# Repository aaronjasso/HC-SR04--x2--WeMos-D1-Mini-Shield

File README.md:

# HC-SR04--x2--WeMos-D1-Mini-Shield
Shield to attach up to two HC-SR04 ultrasonic distance sensors to a Wemos D1 Mini ESP8266 module.

[Sensor datasheet](https://cdn.sparkfun.com/datasheets/Sensors/Proximity/HCSR04.pdf)

[Second datasheet source](https://www.electroschematics.com/8902/hc-sr04-datasheet/)

Works with one or two sensors. The first is mounted to the shield, the second is intended to be mounted elsewhere and connected with a four-conductor cable. It could also be mounted directly to the board facing the opposite direction as the first sensor.

Utilizes a BS138DW SOT-363 chip (which is just two BSS138 N-channel enhanced mode MOSFETs in one package) for level switching the ESP8266's 3.3V trigger pulse up to 5V for the sensors (ref: https://learn.sparkfun.com/tutorials/retired---using-the-logic-level-converter). The down-convert is a simple voltage divider.

All resistors are 0805 size. Resistors on top of board (with the IC) are 10K, resistors on bottom are 20K.

SENSE1 is mounted to the board  
Trigger pin:  D3  
Echo pin:  D4

SENSE2 (optional) can be located off-board  
Trigger pin:  D7  
Echo pin:  D8

The board and SENSE1 have been tested. Example Arduino sketches are in work. Boards available from OSH Park here: https://oshpark.com/shared_projects/YeCIIDGi

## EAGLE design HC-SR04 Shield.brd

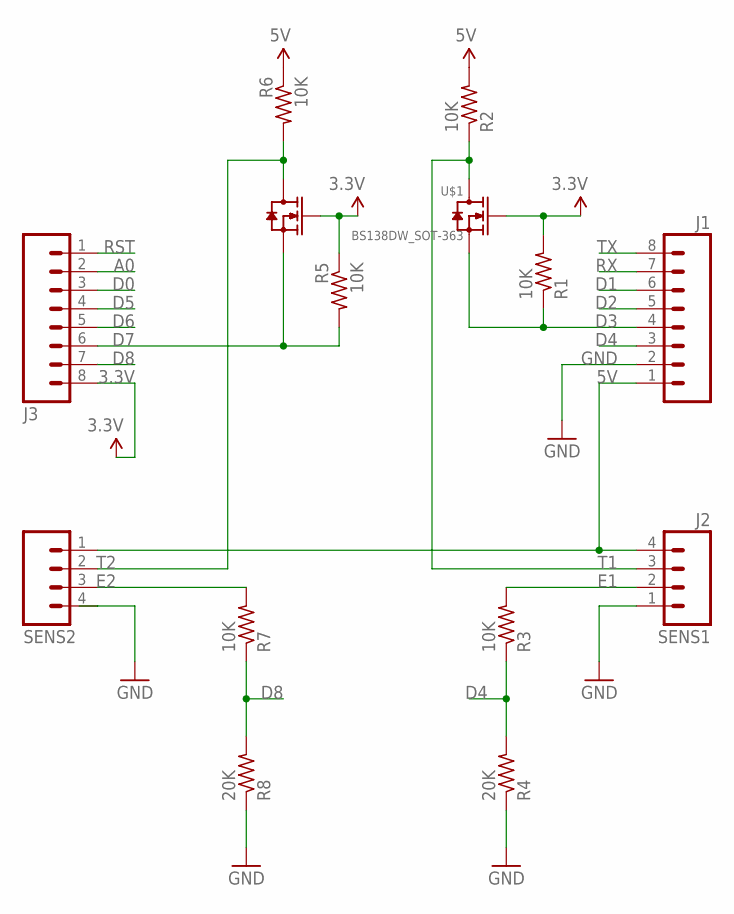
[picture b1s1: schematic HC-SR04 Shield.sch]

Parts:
J1, J3: M08SILK_FEMALE_PTH; 1X08
J2: SENS1; 1X04
R1, R2, R3, R5, R6, R7: 10K; R0805
R4, R8: 20K; R0805
SENS2: M04JST-PTH-VERT; JST-4-PTH-VERT
U$1: BS138DW_SOT-363; SOT363

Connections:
3.3V: J3.8, R1.2, R5.1, U$1.2 (G1), U$1.5 (G)
5V: J1.1, J2.4, R2.2, R6.1, SENS2.1
A0: J3.2
D0: J3.3
D1: J1.6
D2: J1.5
D3: J1.4, R1.1, U$1.4 (S)
D4: J1.3, R3.1, R4.2
D5: J3.4
D6: J3.5
D7: J3.6, R5.2, U$1.1 (S1)
D8: J3.7, R7.1, R8.2
E1: J2.2, R3.2
E2: R7.2, SENS2.3
GND: J1.2, J2.1, R4.1, R8.1, SENS2.4
RST: J3.1
RX: J1.7
T1: J2.3, R2.1, U$1.3 (D)
T2: R6.2, SENS2.2, U$1.6 (D1)
TX: J1.8

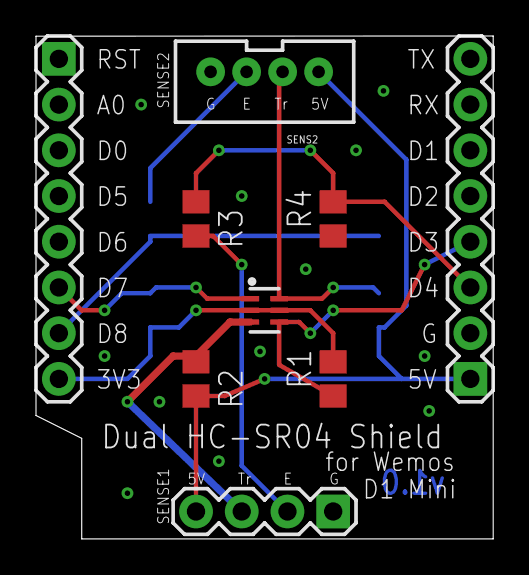
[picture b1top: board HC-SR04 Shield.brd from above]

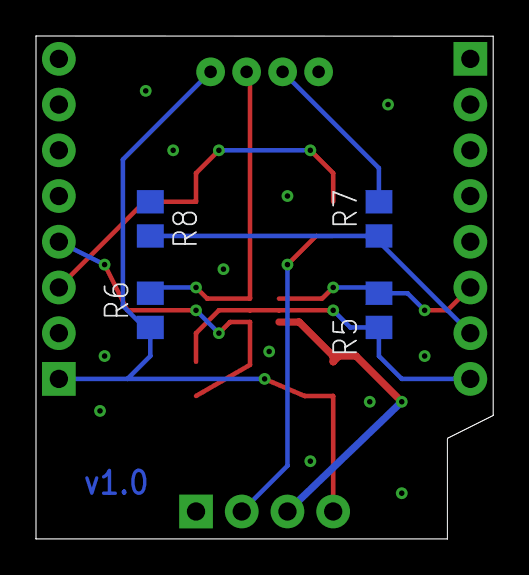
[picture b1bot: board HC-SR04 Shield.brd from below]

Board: 2 copper layers, 25.4 x 27.9 mm, 13 parts (4 on the bottom side), 11 nets.

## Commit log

2016-09-26 :lollipop: Added .gitattributes & .gitignore files
2016-09-26 Eagle 7.6.0 files
2016-09-28 Revert "Updated Readme"
    This reverts commit f784514c2abb25c6023511ac0a71f2df59571b09.
2016-09-28 Revert "Revert "Updated Readme""
    This reverts commit fd0ff574a56911917b617e1d9172e168719a2c59.
2016-09-28 Ignore EAGLE backup files
    I'm a n00b
2016-09-28 Initial test Arduino Sketch (in work)
2016-09-28 Remove versions from filenames
    Apparently this is a n00b mistake. Thanks James!
2016-09-28 Added OSH Park link
2016-09-30 Latest EAGLE file save
2016-10-26 Add images
    Created "extras" folder and added images of board top, bottom, and an
    assembled board on a D1 Mini with sensor mounted
2016-10-28 Update README
    Added picture of assembled board
2017-04-03 Fixed figure filenames
2018-05-07 Update README.md
    Fixed logic level converter ref. link
2019-07-19 Update README.md
    Fixed broken datasheet link

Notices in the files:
parts and their libraries:
SparkFun-Connectors: Licensing: Creative Commons ShareAlike 4.0 International - https://creativecommons.org/licenses/by-sa/4.0
